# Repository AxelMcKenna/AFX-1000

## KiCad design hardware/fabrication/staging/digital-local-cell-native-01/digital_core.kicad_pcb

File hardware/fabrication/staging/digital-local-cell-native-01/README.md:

# DC02 — local power, filter and reference cells

This selected digital development candidate has **427 missing connections**, down
from 466, with zero native DRC geometry, schematic-parity and ERC findings. Every
native category remains enabled. **Not released for fabrication.**

The 138 electrical parts, five mounts, connector positions, notched 114 × 60 mm
outline and 1.6 mm declared thickness are retained. Three MCP23017 expanders and
39 capacitors/resistors have new explicit sites. The previous expander arrangement
between the Seed solder-pin rows left insufficient nearby space for decouplers.
The ten pot-input filter capacitors now have approximately 2.29 mm local traces
to their Seed pins, instead of 9.6–28.4 mm straight-line separations.

Thirty-nine local connections use 59 new segments and eight 0.60/0.30 mm through
vias. Signal copper remains on the outer faces; both inner layers remain available
for the unfinished power/return design. All eight drilled holes are independently
screened outside front/back SMD copper with at least 0.15 mm hole-edge separation.
This is a geometry screen, not mask-web, plating, registration or stencil approval.

Some local parts use the opposite board face. Their actual routes include the
necessary conventional dogbone vias. The longest current-reference route is
R3002 at 8.864 mm; its placement distance alone must not be used as the routed
length. Its return path and noise sensitivity still require review. The new
connections do not complete ground returns, bulk distribution, exposed-pad
thermal paths, LED current returns or the remaining control/audio/SD signals.

Native source-bound evidence includes [review.json](review.json),
[local-connectivity-review.json](local-connectivity-review.json), the
[additive geometry audit](independent-geometry-audit.json), and
[handoff.json](handoff.json). An independent inverse-transform audit restores all
electrical/mechanical geometry after undoing the 42 declared component changes;
only annotation half-turns are normalized. The full four-sheet schematic is
captured and hashed. The earlier placed-only file lacked persistent pad UUIDs;
the new native checkpoint supplies stable IDs for routing/connectivity evidence.

Both views were inspected at 300 dpi. Thirteen focused integration/audit tests
pass. The [AP02 arrangement](../assembly-layout-02/README.md) rechecks the actual
new poses under the existing conditional receiving limits. Complete installed
fit, actual parts/process acceptance, supply/return and thermal performance,
dynamic fault behavior and final manufacturing/assembly drawings remain open.

The earlier signal-router trial is retained as unselected evidence. Trial 02
incorrectly used reserved inner layers and was rejected. Trial 03 correctly
restricts signal tracks to the outer layers, but uses the superseded remote-cap
placement; its copper is not adopted into DC02.

Revalidate the selected candidate with `python -m hardware.fabrication.audit_scope`.
The next routing capture is `../digital-local-cell-inputs-427/capture.json`.

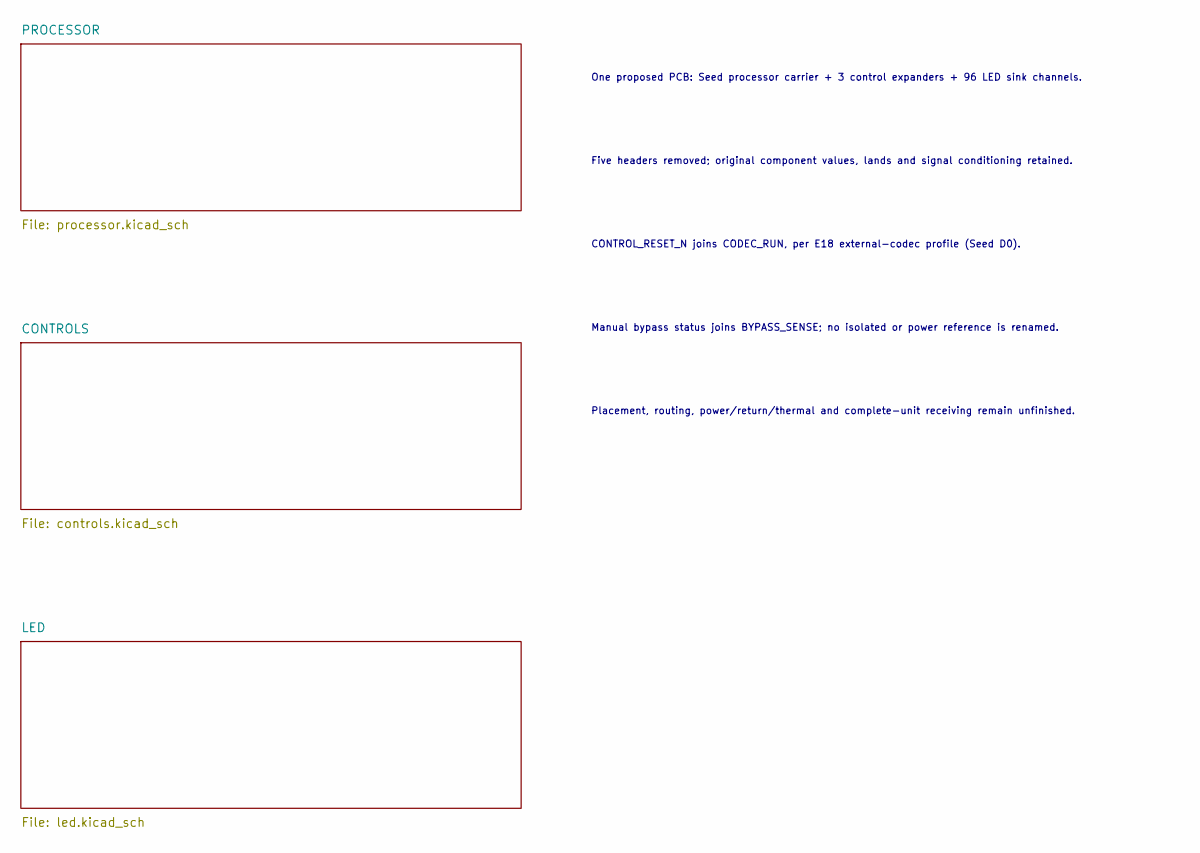
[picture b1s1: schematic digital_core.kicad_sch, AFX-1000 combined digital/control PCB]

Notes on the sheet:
One proposed PCB: Seed processor carrier + 3 control expanders + 96 LED sink channels.
Five headers removed; original component values, lands and signal conditioning retained.
CONTROL_RESET_N joins CODEC_RUN, per E18 external-codec profile (Seed D0).
Manual bypass status joins BYPASS_SENSE; no isolated or power reference is renamed.
Placement, routing, power/return/thermal and complete-unit receiving remain unfinished.

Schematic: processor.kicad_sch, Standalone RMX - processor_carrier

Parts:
C1001: 22uF 25V X7R; C_1210_3225Metric
C1002, C1004, C1006, C1011, C1012, C1013, C1014, C1015, C1016, C1017, C1018, C1019, C1020: 100nF 16V X7R; C_0805_2012Metric
C1003: 1uF 16V X7R; C_0805_2012Metric
C1005: 4.7uF 16V X7R; C_0805_2012Metric
J1001, J1013, J1014, J1015: Alpha6715_AWG18_DIRECT_SOLDER_PROPOSAL; AWG18_Solder_2x1_P4mm_D2p2
J1003, J1006: Header6; PinHeader_1x06_P2.54mm_Vertical
J1004, J1005: Header5; PinHeader_1x05_P2.54mm_Vertical
J1007, J1008: Header2; PinHeader_1x02_P2.54mm_Vertical
J1009, J1010: Header4; PinHeader_1x04_P2.54mm_Vertical
J1012: Header8; PinHeader_1x08_P2.54mm_Vertical
J1020, J1021, J1022, J1023, J1024, J1025, J1026, J1027, J1028, J1029: Header3; PinHeader_1x03_P2.54mm_Vertical
R1001: 0.47R 1% WSLT2512R4700FEA P70=0.815W; WSLT2512_R_2512_Manufacturer
R1002: 10k 1%; R_0805_2012Metric
R1003, R1004, R1005, R1006: 100k 1%; R_0805_2012Metric
R1010, R1011, R1012, R1013, R1014, R1015, R1016, R1017, R1018, R1019, R1020: 33R 1%; R_0805_2012Metric
R1031, R1032, R1033, R1034, R1035, R1036, R1037, R1038, R1039, R1040: 1k 1%; R_0805_2012Metric
R1041, R1042, R1043, R1044, R1045, R1046, R1047, R1048, R1049, R1050: 1M 1%; R_0805_2012Metric
U1001: DaisySeed3; Seed3_Socket40

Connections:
5V_DIG: J1001.1, J1013.1, J1014.1, J1015.1, R1001.1; also elsewhere on the board
/PROCESSOR/ADC_DATA: J1005.4, U1001.32 (D25_ADC_DATA)
/PROCESSOR/ARMED: J1003.5, R1005.1, U1001.37 (D30_ARMED)
/PROCESSOR/BCLK: J1005.2, U1001.35 (D28_BCLK)
/PROCESSOR/DAC_DATA: J1005.5, R1014.2
/PROCESSOR/DAC_DATA_SRC: R1014.1, U1001.33 (D26_DAC_DATA)
/PROCESSOR/GAIN_REQ: J1003.4, R1004.1, U1001.10 (D9)
/PROCESSOR/HEARTBEAT: J1003.2, U1001.14 (D13)
/PROCESSOR/LED_BLANK_SRC: R1013.1, U1001.15 (D14)
/PROCESSOR/LED_MOSI_SRC: R1012.1, U1001.11 (D10)
/PROCESSOR/LED_SCK_SRC: R1011.1, U1001.9 (D8)
/PROCESSOR/LED_XLAT_SRC: R1010.1, U1001.8 (D7)
/PROCESSOR/MCU_PERMIT: J1003.3, R1003.1, U1001.36 (D29_PERMIT)
/PROCESSOR/POT_ADC_00: C1011.1, R1031.2, R1041.1, U1001.22 (D15)
/PROCESSOR/POT_ADC_01: C1012.1, R1032.2, R1042.1, U1001.23 (D16)
/PROCESSOR/POT_ADC_02: C1013.1, R1033.2, R1043.1, U1001.24 (D17)
/PROCESSOR/POT_ADC_03: C1014.1, R1034.2, R1044.1, U1001.25 (D18)
/PROCESSOR/POT_ADC_04: C1015.1, R1035.2, R1045.1, U1001.26 (D19)
/PROCESSOR/POT_ADC_05: C1016.1, R1036.2, R1046.1, U1001.27 (D20)
/PROCESSOR/POT_ADC_06: C1017.1, R1037.2, R1047.1, U1001.28 (D21)
/PROCESSOR/POT_ADC_07: C1018.1, R1038.2, R1048.1, U1001.29 (D22)
/PROCESSOR/POT_ADC_08: C1019.1, R1039.2, R1049.1, U1001.30 (D23)
/PROCESSOR/POT_ADC_09: C1020.1, R1040.2, R1050.1, U1001.31 (D24)
/PROCESSOR/POT_RAW_00: J1020.2, R1031.1
/PROCESSOR/POT_RAW_01: J1021.2, R1032.1
/PROCESSOR/POT_RAW_02: J1022.2, R1033.1
/PROCESSOR/POT_RAW_03: J1023.2, R1034.1
/PROCESSOR/POT_RAW_04: J1024.2, R1035.1
/PROCESSOR/POT_RAW_05: J1025.2, R1036.1
/PROCESSOR/POT_RAW_06: J1026.2, R1037.1
/PROCESSOR/POT_RAW_07: J1027.2, R1038.1
/PROCESSOR/POT_RAW_08: J1028.2, R1039.1
/PROCESSOR/POT_RAW_09: J1029.2, R1040.1
/PROCESSOR/SDMMC_CLK: J1012.8, R1020.2
/PROCESSOR/SDMMC_CLK_SRC: R1020.1, U1001.7 (D6)
/PROCESSOR/SDMMC_CMD: J1012.7, R1019.2
/PROCESSOR/SDMMC_CMD_SRC: R1019.1, U1001.6 (D5)
/PROCESSOR/SDMMC_D0: J1012.3, R1015.2
/PROCESSOR/SDMMC_D0_SRC: R1015.1, U1001.5 (D4)
/PROCESSOR/SDMMC_D1: J1012.4, R1016.2
/PROCESSOR/SDMMC_D1_SRC: R1016.1, U1001.4 (D3)
/PROCESSOR/SDMMC_D2: J1012.5, R1017.2
/PROCESSOR/SDMMC_D2_SRC: R1017.1, U1001.3 (D2)
/PROCESSOR/SDMMC_D3: J1012.6, R1018.2
/PROCESSOR/SDMMC_D3_SRC: R1018.1, U1001.2 (D1)
/PROCESSOR/SEED_VIN: C1001.1, C1002.1, R1001.2, U1001.39 (VIN)
/PROCESSOR/V3V3_ANALOG: C1003.1, C1004.1, J1020.3, J1021.3, J1022.3, J1023.3, J1024.3, J1025.3, J1026.3, J1027.3, J1028.3, J1029.3, U1001.21 (3V3_ANALOG)
/PROCESSOR/WS: J1005.3, U1001.34 (D27_WS)
AGND: C1001.2, C1002.2, C1003.2, C1004.2, C1005.2, C1006.2, C1011.2, C1012.2, C1013.2, C1014.2, C1015.2, C1016.2, C1017.2, C1018.2, C1019.2, C1020.2, J1001.2, J1003.1, J1004.1, J1005.1, J1006.1, J1007.1, J1008.1, J1009.1, J1010.1, J1012.1, J1013.2, J1014.2, J1015.2, J1020.1, J1021.1, J1022.1, J1023.1, J1024.1, J1025.1, J1026.1, J1027.1, J1028.1, J1029.1, R1003.2, R1004.2, R1005.2, R1006.2, R1041.2, R1042.2, R1043.2, R1044.2, R1045.2, R1046.2, R1047.2, R1048.2, R1049.2, R1050.2, U1001.20 (AGND), U1001.40 (DGND); also elsewhere on the board
ANALOG_OK: J1004.4, J1006.6; also elsewhere on the board
BYPASS_SENSE: J1003.6, J1004.3; also elsewhere on the board
CODEC_RUN: J1006.5, R1006.1, U1001.1 (D0); also elsewhere on the board
INPUT_READY: J1004.5, J1007.2; also elsewhere on the board
LED_BLANK: R1002.1, R1013.2; also elsewhere on the board
LED_MOSI: R1012.2; also elsewhere on the board
LED_SCK: R1011.2; also elsewhere on the board
LED_XLAT: R1010.2; also elsewhere on the board
MODE_SEND_RETURN: J1004.2, J1008.2; also elsewhere on the board
SCL: J1006.3, J1009.3, J1010.3, U1001.12 (D11); also elsewhere on the board
SDA: J1006.4, J1009.4, J1010.4, U1001.13 (D12); also elsewhere on the board
V3V3_IO: C1005.1, C1006.1, J1006.2, J1009.2, J1010.2, J1012.2, R1002.2, U1001.38 (3V3_DIGITAL); also elsewhere on the board

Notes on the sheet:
E19 - external-profile Seed3 processor carrier.40 module pins,10 analog pots,control-hub/codec/relay/LED/sensor/SD interfaces.
3.3V outputs are separate: analog pin21 excites pots; digital pin38 powers shared logic. AGND and DGND join on carrier.
Routed150x65mm carrier: front-slot Seed and2mm E18 daughterboard shift implemented in PCB/A05 CAD; physical assembly unverified.
No whole-bus/3.3V load, USB partial-power/backfeed, ADC acquisition/accuracy, SDMMC SI or physical fit approval. No fabrication release.

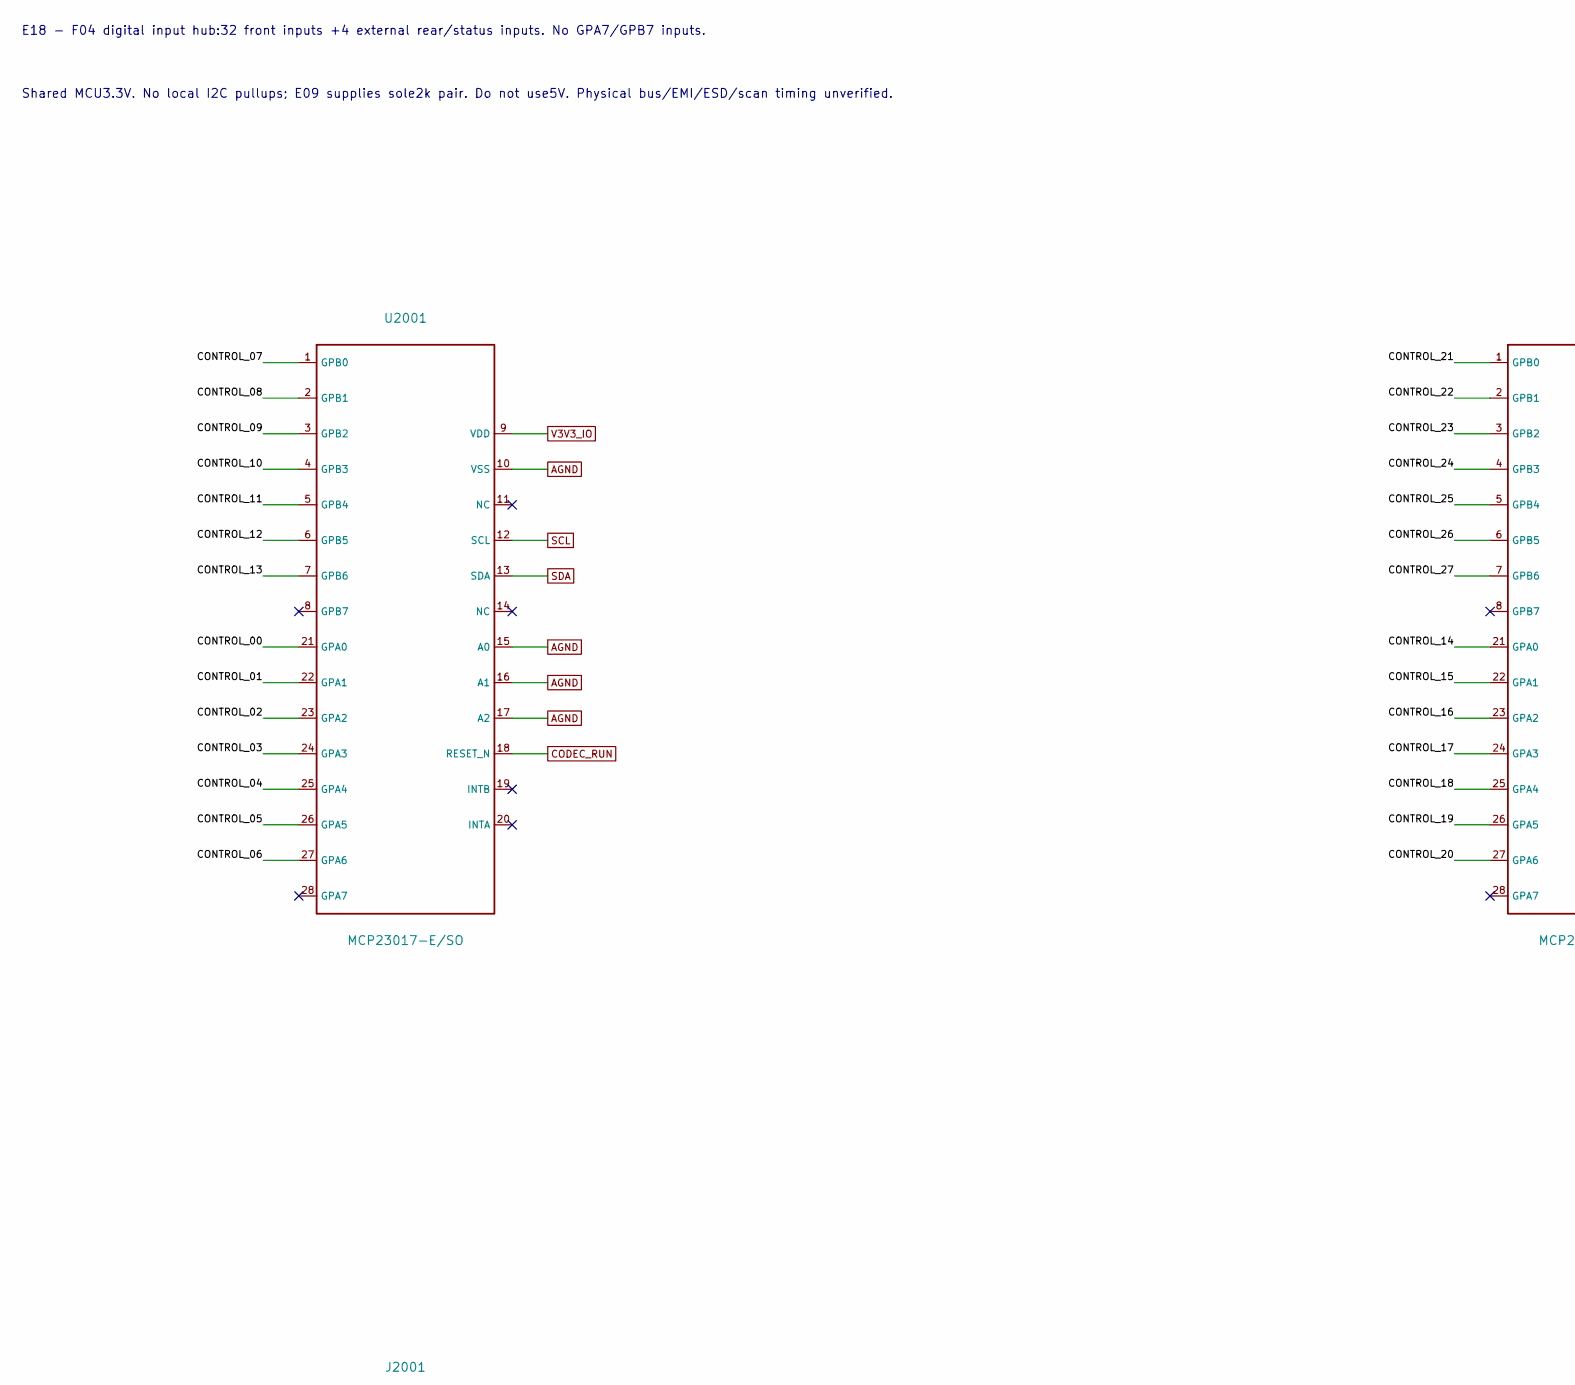
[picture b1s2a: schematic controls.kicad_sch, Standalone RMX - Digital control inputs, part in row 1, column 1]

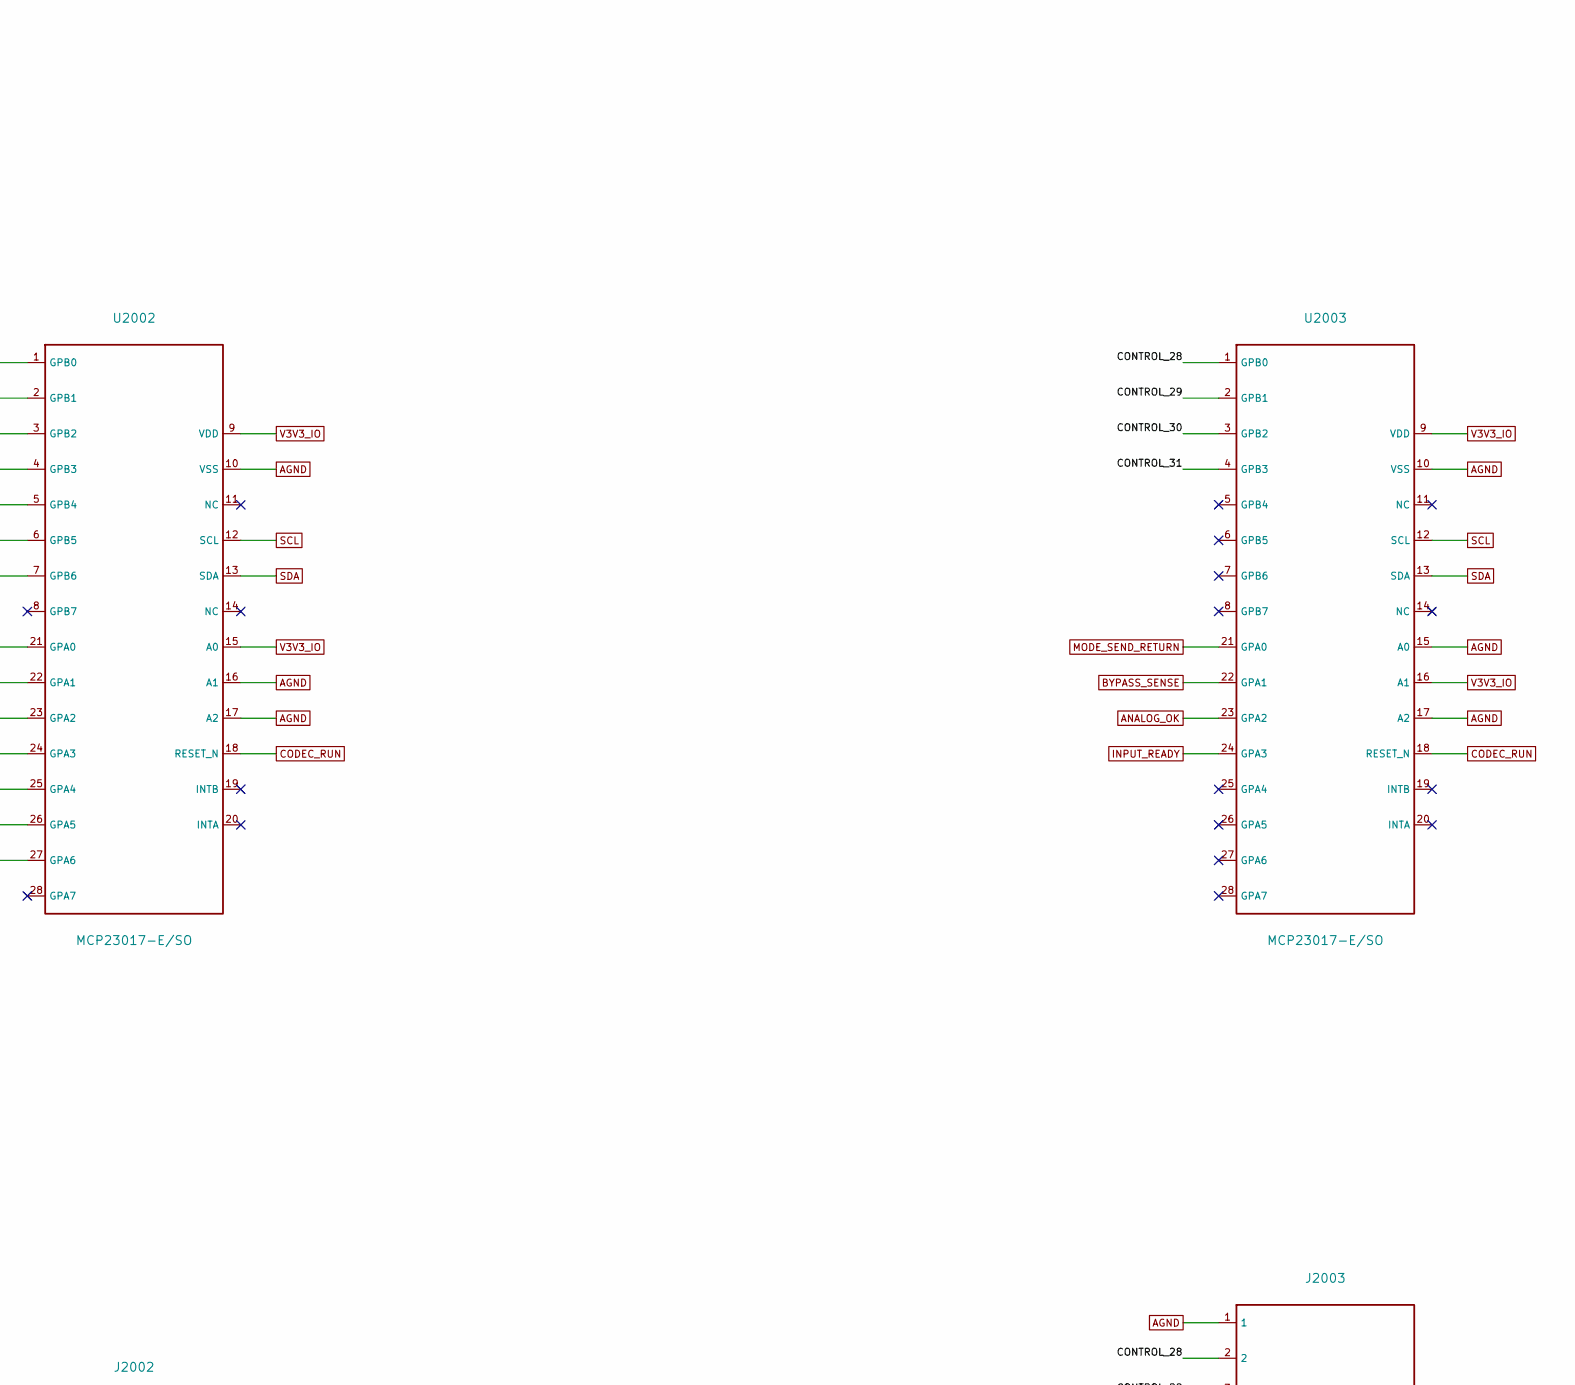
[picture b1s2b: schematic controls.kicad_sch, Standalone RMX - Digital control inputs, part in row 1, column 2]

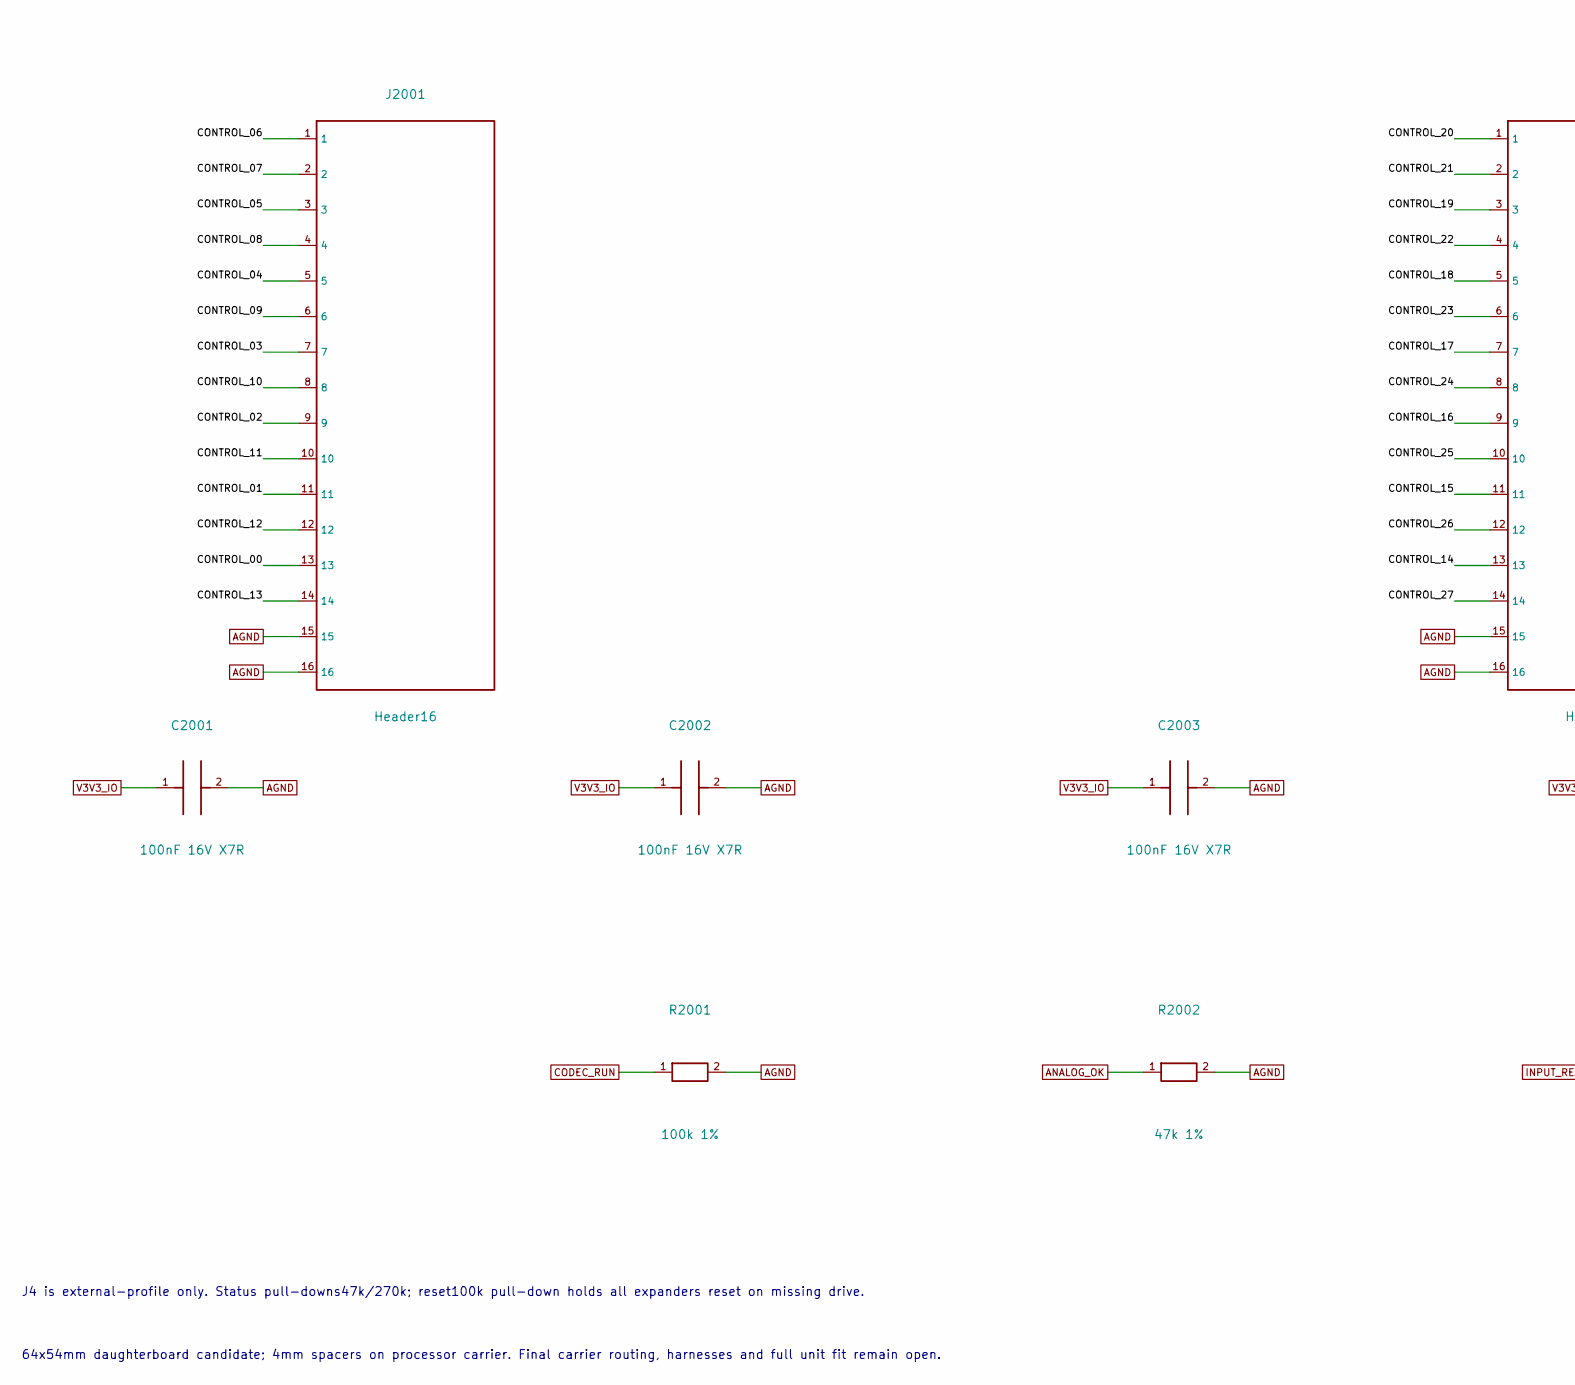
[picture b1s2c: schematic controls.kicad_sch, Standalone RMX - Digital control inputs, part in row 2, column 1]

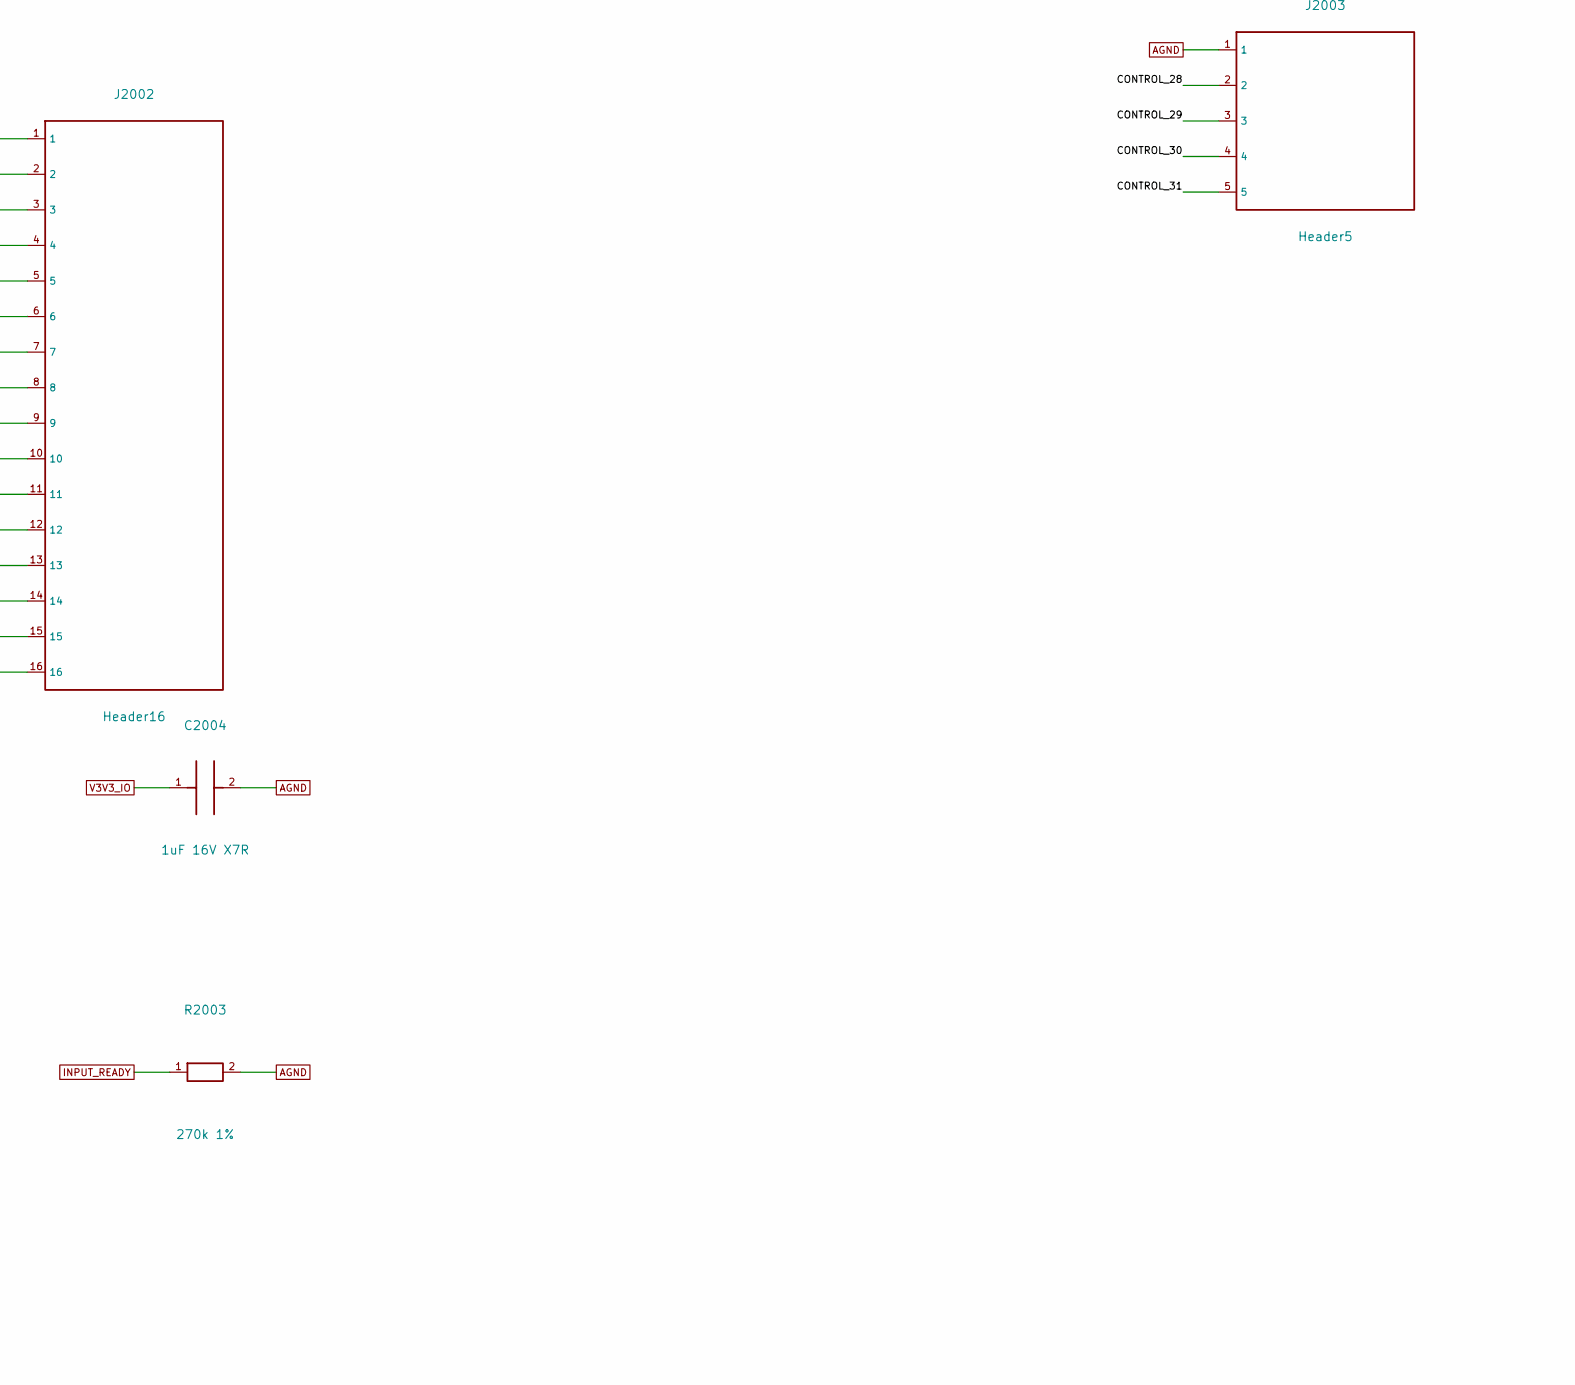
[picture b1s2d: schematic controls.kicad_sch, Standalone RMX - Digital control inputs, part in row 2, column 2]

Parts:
C2001, C2002, C2003: 100nF 16V X7R; C_0805_2012Metric
C2004: 1uF 16V X7R; C_0805_2012Metric
J2001, J2002: Header16; PinHeader_2x08_P2.54mm_Vertical
J2003: Header5; PinHeader_1x05_P2.54mm_Vertical
R2001: 100k 1%; R_0805_2012Metric
R2002: 47k 1%; R_0805_2012Metric
R2003: 270k 1%; R_0805_2012Metric
U2001, U2002, U2003: MCP23017-E/SO; SOIC-28W_7.5x17.9mm_P1.27mm

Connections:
/CONTROLS/CONTROL_00: J2001.13, U2001.21 (GPA0)
/CONTROLS/CONTROL_01: J2001.11, U2001.22 (GPA1)
/CONTROLS/CONTROL_02: J2001.9, U2001.23 (GPA2)
/CONTROLS/CONTROL_03: J2001.7, U2001.24 (GPA3)
/CONTROLS/CONTROL_04: J2001.5, U2001.25 (GPA4)
/CONTROLS/CONTROL_05: J2001.3, U2001.26 (GPA5)
/CONTROLS/CONTROL_06: J2001.1, U2001.27 (GPA6)
/CONTROLS/CONTROL_07: J2001.2, U2001.1 (GPB0)
/CONTROLS/CONTROL_08: J2001.4, U2001.2 (GPB1)
/CONTROLS/CONTROL_09: J2001.6, U2001.3 (GPB2)
/CONTROLS/CONTROL_10: J2001.8, U2001.4 (GPB3)
/CONTROLS/CONTROL_11: J2001.10, U2001.5 (GPB4)
/CONTROLS/CONTROL_12: J2001.12, U2001.6 (GPB5)
/CONTROLS/CONTROL_13: J2001.14, U2001.7 (GPB6)
/CONTROLS/CONTROL_14: J2002.13, U2002.21 (GPA0)
/CONTROLS/CONTROL_15: J2002.11, U2002.22 (GPA1)
/CONTROLS/CONTROL_16: J2002.9, U2002.23 (GPA2)
/CONTROLS/CONTROL_17: J2002.7, U2002.24 (GPA3)
/CONTROLS/CONTROL_18: J2002.5, U2002.25 (GPA4)
/CONTROLS/CONTROL_19: J2002.3, U2002.26 (GPA5)
/CONTROLS/CONTROL_20: J2002.1, U2002.27 (GPA6)
/CONTROLS/CONTROL_21: J2002.2, U2002.1 (GPB0)
/CONTROLS/CONTROL_22: J2002.4, U2002.2 (GPB1)
/CONTROLS/CONTROL_23: J2002.6, U2002.3 (GPB2)
/CONTROLS/CONTROL_24: J2002.8, U2002.4 (GPB3)
/CONTROLS/CONTROL_25: J2002.10, U2002.5 (GPB4)
/CONTROLS/CONTROL_26: J2002.12, U2002.6 (GPB5)
/CONTROLS/CONTROL_27: J2002.14, U2002.7 (GPB6)
/CONTROLS/CONTROL_28: J2003.2, U2003.1 (GPB0)
/CONTROLS/CONTROL_29: J2003.3, U2003.2 (GPB1)
/CONTROLS/CONTROL_30: J2003.4, U2003.3 (GPB2)
/CONTROLS/CONTROL_31: J2003.5, U2003.4 (GPB3)
AGND: C2001.2, C2002.2, C2003.2, C2004.2, J2001.15, J2001.16, J2002.15, J2002.16, J2003.1, R2001.2, R2002.2, R2003.2, U2001.10 (VSS), U2001.15 (A0), U2001.16 (A1), U2001.17 (A2), U2002.10 (VSS), U2002.16 (A1), U2002.17 (A2), U2003.10 (VSS), U2003.15 (A0), U2003.17 (A2); also elsewhere on the board
ANALOG_OK: R2002.1, U2003.23 (GPA2); also elsewhere on the board
BYPASS_SENSE: U2003.22 (GPA1); also elsewhere on the board
CODEC_RUN: R2001.1, U2001.18 (RESET_N), U2002.18 (RESET_N), U2003.18 (RESET_N); also elsewhere on the board
INPUT_READY: R2003.1, U2003.24 (GPA3); also elsewhere on the board
MODE_SEND_RETURN: U2003.21 (GPA0); also elsewhere on the board
SCL: U2001.12 (SCL), U2002.12 (SCL), U2003.12 (SCL); also elsewhere on the board
SDA: U2001.13 (SDA), U2002.13 (SDA), U2003.13 (SDA); also elsewhere on the board
V3V3_IO: C2001.1, C2002.1, C2003.1, C2004.1, U2001.9 (VDD), U2002.9 (VDD), U2002.15 (A0), U2003.9 (VDD), U2003.16 (A1); also elsewhere on the board

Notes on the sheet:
E18 - F04 digital input hub:32 front inputs +4 external rear/status inputs. No GPA7/GPB7 inputs.
Shared MCU3.3V. No local I2C pullups; E09 supplies sole2k pair. Do not use5V. Physical bus/EMI/ESD/scan timing unverified.
J4 is external-profile only. Status pull-downs47k/270k; reset100k pull-down holds all expanders reset on missing drive.
64x54mm daughterboard candidate; 4mm spacers on processor carrier. Final carrier routing, harnesses and full unit fit remain open.

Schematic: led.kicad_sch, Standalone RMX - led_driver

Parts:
C3001, C3003, C3005, C3007, C3009, C3010, C3011, C3012: 100nF 16V X7R; C_0603_1608Metric
C3002, C3004, C3006, C3008, C3014: 4.7uF 16V X7R; C_0805_2012Metric
C3013: 22uF 25V X7R; C_1210_3225Metric
J3002, J3003, J3004, J3005: Header26; PinHeader_2x13_P2.54mm_Vertical
Q3001, Q3002: AO3400A; SOT-23
R3001, R3002, R3003, R3004: 16.5k 1%; R_0603_1608Metric
R3005: 47k 1%; R_0603_1608Metric
R3006, R3007, R3010, R3011: 10k 1%; R_0603_1608Metric
R3008, R3009, R3012, R3013, R3014, R3019, R3020, R3021: 100k 1%; R_0603_1608Metric
R3015, R3016, R3017, R3018: 33R 1%; R_0603_1608Metric
U3001, U3002, U3003, U3004: TLC5947DAPR; TLC5947_DAP0032C
U3005: SN74LVC8T245PWR; TSSOP-24_4.4x7.8mm_P0.65mm
U3006: TPS3808G33DBVR; SOT-23-6
U3007: TPS3808G50DBVR; SOT-23-6

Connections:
5V_DIG: C3001.1, C3002.1, C3003.1, C3004.1, C3005.1, C3006.1, C3007.1, C3008.1, C3010.1, C3012.1, C3013.1, C3014.1, J3002.25, J3002.26, J3003.25, J3003.26, J3004.25, J3004.26, J3005.25, J3005.26, R3007.2, R3011.2, U3001.32 (VCC), U3002.32 (VCC), U3003.32 (VCC), U3004.32 (VCC), U3005.23 (VCCB), U3005.24 (VCCB), U3007.3 (MR_N), U3007.5 (SENSE), U3007.6 (VDD); also elsewhere on the board
/LED/BLANK_5V: R3011.1, R3018.2, U3001.2 (BLANK), U3002.2 (BLANK), U3003.2 (BLANK), U3004.2 (BLANK)
/LED/BLANK_5V_SRC: R3018.1, U3005.18 (B4)
/LED/CLOCK_5V: R3013.1, R3016.2, U3001.3 (SCLK), U3002.3 (SCLK), U3003.3 (SCLK), U3004.3 (SCLK)
/LED/CLOCK_5V_SRC: R3016.1, U3005.20 (B2)
/LED/DATA_5V: R3012.1, R3015.2, U3001.4 (SIN)
/LED/DATA_5V_SRC: R3015.1, U3005.21 (B1)
/LED/ENABLE_MID: Q3001.2 (S), Q3002.3 (D)
/LED/IREF_0: R3001.1, U3001.31 (IREF)
/LED/IREF_1: R3002.1, U3002.31 (IREF)
/LED/IREF_2: R3003.1, U3003.31 (IREF)
/LED/IREF_3: R3004.1, U3004.31 (IREF)
/LED/LATCH_5V: R3014.1, R3017.2, U3001.30 (XLAT), U3002.30 (XLAT), U3003.30 (XLAT), U3004.30 (XLAT)
/LED/LATCH_5V_SRC: R3017.1, U3005.19 (B3)
/LED/LED_00: J3003.1, U3001.5 (OUT0)
/LED/LED_01: J3003.2, U3001.6 (OUT1)
/LED/LED_02: J3003.3, U3001.7 (OUT2)
/LED/LED_03: J3003.4, U3001.8 (OUT3)
/LED/LED_04: J3003.5, U3001.9 (OUT4)
/LED/LED_05: J3003.6, U3001.10 (OUT5)
/LED/LED_06: J3003.7, U3001.11 (OUT6)
/LED/LED_07: J3003.8, U3001.12 (OUT7)
/LED/LED_08: J3003.9, U3001.13 (OUT8)
/LED/LED_09: J3003.10, U3001.14 (OUT9)
/LED/LED_10: J3003.11, U3001.15 (OUT10)
/LED/LED_11: J3003.12, U3001.16 (OUT11)
/LED/LED_12: J3002.12, U3001.17 (OUT12)
/LED/LED_13: J3002.11, U3001.18 (OUT13)
/LED/LED_14: J3002.10, U3001.19 (OUT14)
/LED/LED_15: J3002.9, U3001.20 (OUT15)
/LED/LED_16: J3002.8, U3001.21 (OUT16)
/LED/LED_17: J3002.7, U3001.22 (OUT17)
/LED/LED_18: J3002.6, U3001.23 (OUT18)
/LED/LED_19: J3002.5, U3001.24 (OUT19)
/LED/LED_20: J3002.4, U3001.25 (OUT20)
/LED/LED_21: J3002.3, U3001.26 (OUT21)
/LED/LED_22: J3002.2, U3001.27 (OUT22)
/LED/LED_23: J3002.1, U3001.28 (OUT23)
/LED/LED_24: J3003.13, U3002.5 (OUT0)
/LED/LED_25: J3003.14, U3002.6 (OUT1)
/LED/LED_26: J3003.15, U3002.7 (OUT2)
/LED/LED_27: J3003.16, U3002.8 (OUT3)
/LED/LED_28: J3003.17, U3002.9 (OUT4)
/LED/LED_29: J3003.18, U3002.10 (OUT5)
/LED/LED_30: J3003.19, U3002.11 (OUT6)
/LED/LED_31: J3003.20, U3002.12 (OUT7)
/LED/LED_32: J3003.21, U3002.13 (OUT8)
/LED/LED_33: J3003.22, U3002.14 (OUT9)
/LED/LED_34: J3003.23, U3002.15 (OUT10)
/LED/LED_35: J3003.24, U3002.16 (OUT11)
/LED/LED_36: J3002.24, U3002.17 (OUT12)
/LED/LED_37: J3002.23, U3002.18 (OUT13)
/LED/LED_38: J3002.22, U3002.19 (OUT14)
/LED/LED_39: J3002.21, U3002.20 (OUT15)
/LED/LED_40: J3002.20, U3002.21 (OUT16)
/LED/LED_41: J3002.19, U3002.22 (OUT17)
/LED/LED_42: J3002.18, U3002.23 (OUT18)
/LED/LED_43: J3002.17, U3002.24 (OUT19)
/LED/LED_44: J3002.16, U3002.25 (OUT20)
/LED/LED_45: J3002.15, U3002.26 (OUT21)
/LED/LED_46: J3002.14, U3002.27 (OUT22)
/LED/LED_47: J3002.13, U3002.28 (OUT23)
/LED/LED_48: J3005.1, U3003.5 (OUT0)
/LED/LED_49: J3005.2, U3003.6 (OUT1)
/LED/LED_50: J3005.3, U3003.7 (OUT2)
/LED/LED_51: J3005.4, U3003.8 (OUT3)
/LED/LED_52: J3005.5, U3003.9 (OUT4)
/LED/LED_53: J3005.6, U3003.10 (OUT5)
/LED/LED_54: J3005.7, U3003.11 (OUT6)
/LED/LED_55: J3005.8, U3003.12 (OUT7)
/LED/LED_56: J3005.9, U3003.13 (OUT8)
/LED/LED_57: J3005.10, U3003.14 (OUT9)
/LED/LED_58: J3005.11, U3003.15 (OUT10)
/LED/LED_59: J3005.12, U3003.16 (OUT11)
/LED/LED_60: J3004.12, U3003.17 (OUT12)
/LED/LED_61: J3004.11, U3003.18 (OUT13)
/LED/LED_62: J3004.10, U3003.19 (OUT14)
/LED/LED_63: J3004.9, U3003.20 (OUT15)
/LED/LED_64: J3004.8, U3003.21 (OUT16)
/LED/LED_65: J3004.7, U3003.22 (OUT17)
/LED/LED_66: J3004.6, U3003.23 (OUT18)
/LED/LED_67: J3004.5, U3003.24 (OUT19)
/LED/LED_68: J3004.4, U3003.25 (OUT20)
/LED/LED_69: J3004.3, U3003.26 (OUT21)
/LED/LED_70: J3004.2, U3003.27 (OUT22)
/LED/LED_71: J3004.1, U3003.28 (OUT23)
/LED/LED_72: J3005.13, U3004.5 (OUT0)
/LED/LED_73: J3005.14, U3004.6 (OUT1)
/LED/LED_74: J3005.15, U3004.7 (OUT2)
/LED/LED_75: J3005.16, U3004.8 (OUT3)
/LED/LED_76: J3005.17, U3004.9 (OUT4)
/LED/LED_77: J3005.18, U3004.10 (OUT5)
/LED/LED_78: J3005.19, U3004.11 (OUT6)
/LED/LED_79: J3005.20, U3004.12 (OUT7)
/LED/LED_80: J3005.21, U3004.13 (OUT8)
/LED/LED_81: J3005.22, U3004.14 (OUT9)
/LED/LED_82: J3005.23, U3004.15 (OUT10)
/LED/LED_83: J3005.24, U3004.16 (OUT11)
/LED/LED_84: J3004.24, U3004.17 (OUT12)
/LED/LED_85: J3004.23, U3004.18 (OUT13)
/LED/LED_86: J3004.22, U3004.19 (OUT14)
/LED/LED_87: J3004.21, U3004.20 (OUT15)
/LED/LED_88: J3004.20, U3004.21 (OUT16)
/LED/LED_89: J3004.19, U3004.22 (OUT17)
/LED/LED_90: J3004.18, U3004.23 (OUT18)
/LED/LED_91: J3004.17, U3004.24 (OUT19)
/LED/LED_92: J3004.16, U3004.25 (OUT20)
/LED/LED_93: J3004.15, U3004.26 (OUT21)
/LED/LED_94: J3004.14, U3004.27 (OUT22)
/LED/LED_95: J3004.13, U3004.28 (OUT23)
/LED/OE_N: Q3001.3 (D), R3005.1, U3005.22 (OE_N)
/LED/PG_3V3: Q3001.1 (G), R3006.1, R3008.1, U3006.1 (RESET_N)
/LED/PG_5V: Q3002.1 (G), R3007.1, R3009.1, U3007.1 (RESET_N)
/LED/SERIAL_0: U3001.29 (SOUT), U3002.4 (SIN)
/LED/SERIAL_1: U3002.29 (SOUT), U3003.4 (SIN)
/LED/SERIAL_2: U3003.29 (SOUT), U3004.4 (SIN)
AGND: C3001.2, C3002.2, C3003.2, C3004.2, C3005.2, C3006.2, C3007.2, C3008.2, C3009.2, C3010.2, C3011.2, C3012.2, C3013.2, C3014.2, Q3002.2 (S), R3001.2, R3002.2, R3003.2, R3004.2, R3008.2, R3009.2, R3012.2, R3013.2, R3014.2, R3019.2, R3020.2, R3021.2, U3001.1 (GND), U3001.33 (EP), U3002.1 (GND), U3002.33 (EP), U3003.1 (GND), U3003.33 (EP), U3004.1 (GND), U3004.33 (EP), U3005.7 (A5), U3005.8 (A6), U3005.9 (A7), U3005.10 (A8), U3005.11 (GND), U3005.12 (GND), U3005.13 (GND), U3006.2 (GND), U3007.2 (GND); also elsewhere on the board
LED_BLANK: R3010.1, U3005.6 (A4); also elsewhere on the board
LED_MOSI: R3019.1, U3005.3 (A1); also elsewhere on the board
LED_SCK: R3020.1, U3005.4 (A2); also elsewhere on the board
LED_XLAT: R3021.1, U3005.5 (A3); also elsewhere on the board
V3V3_IO: C3009.1, C3011.1, R3005.2, R3006.2, R3010.2, U3005.1 (VCCA), U3005.2 (DIR), U3006.3 (MR_N), U3006.5 (SENSE), U3006.6 (VDD); also elsewhere on the board

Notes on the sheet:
E20 -96-channel constant-current LED/display driver. MCU->U1->U2->U3->U4; global n uses chip n/24 and OUT(n%24).
5V powers driver logic and common anodes; dual-supply translator isolates processor3.3V. Both rails must qualify before outputs enable.
Proposed91x27mm PCB at(197,77), seat6.5mm beneath scene controls; exact footprints/PCB/fit remain to be verified.
3mA is nominal, not a guaranteed low-current bound. E14/E17 digital power budget must include driver ICC. No fabrication or physical validation approval.

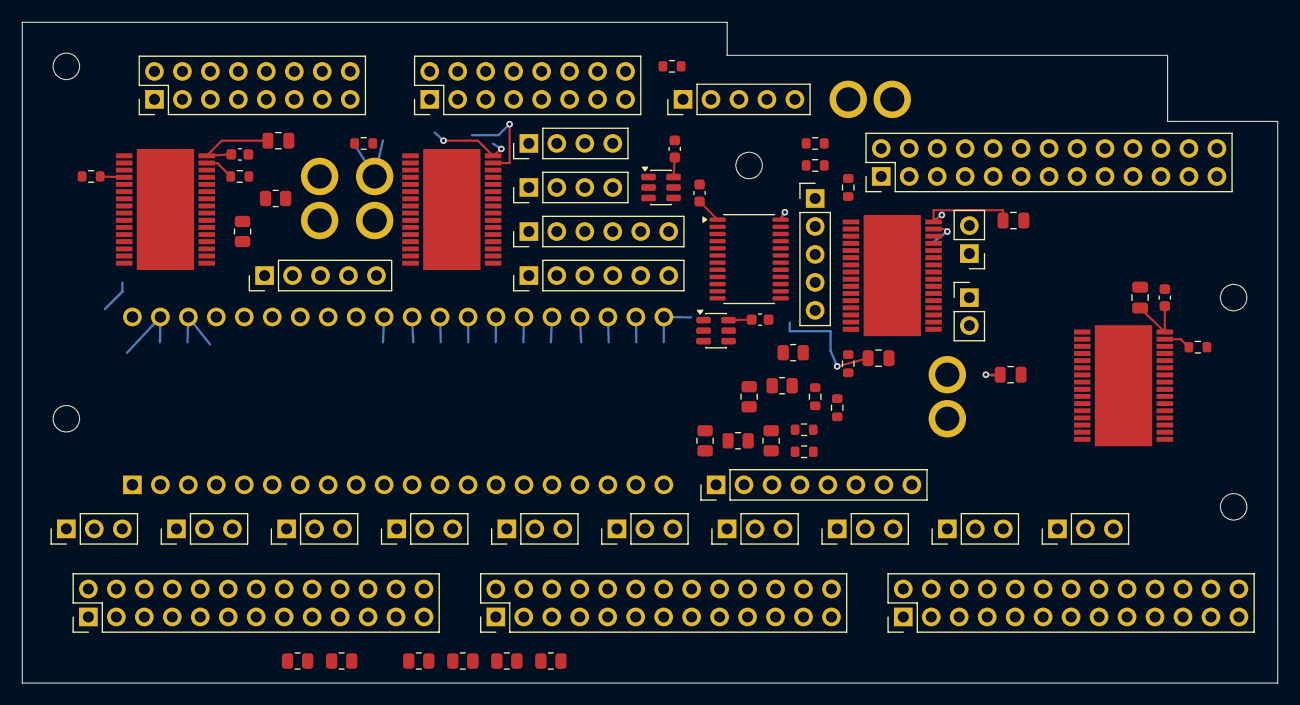
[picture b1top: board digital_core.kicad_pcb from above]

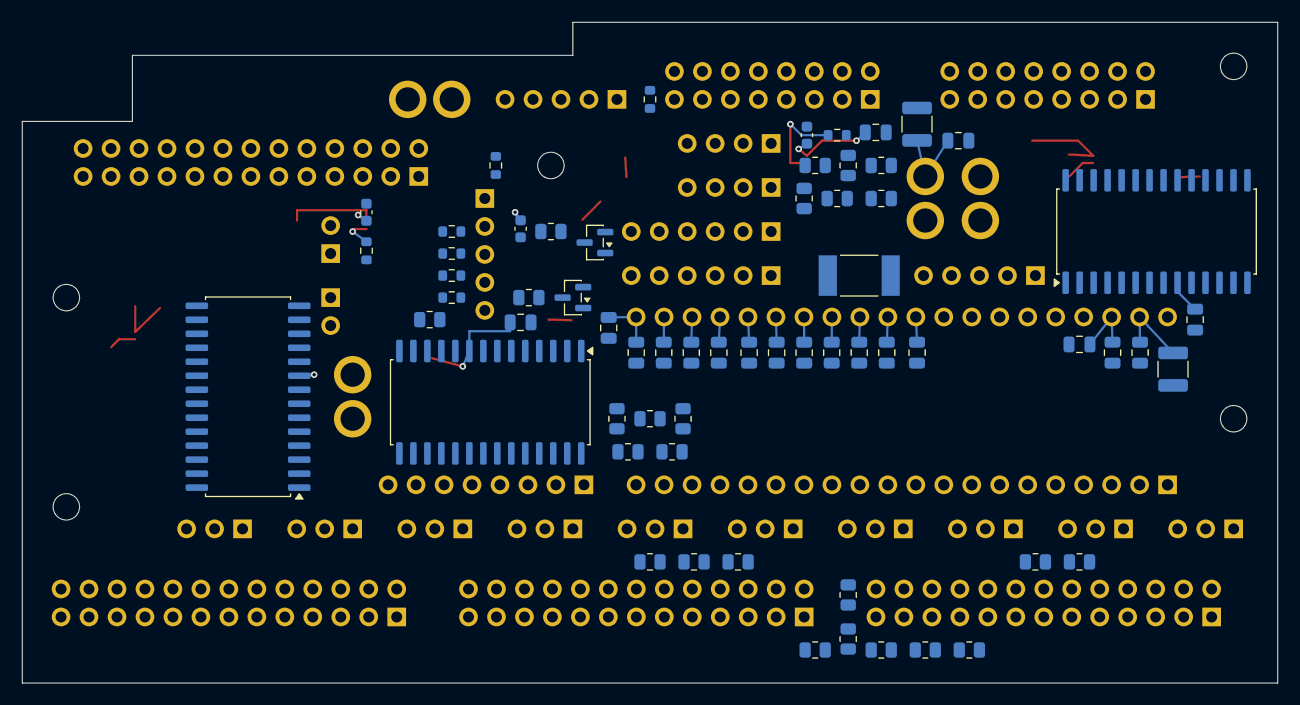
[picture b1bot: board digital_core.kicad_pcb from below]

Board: 4 copper layers, 114.0 x 60.0 mm, 143 parts (63 on the bottom side), 208 nets.

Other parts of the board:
H1, H2, H3, H4, H5: M2_CLEARANCE; M2_Clearance

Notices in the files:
parts and their libraries:
Seed3 + 2xSSW-120-02-G-S: official Daisy pad centers/numbering, 1.04mm socket holes per Samtec ssw-s.pdf. Seed3/USB/stack bounds modeled separately. Electrosmith MIT license in vendor/Electrosmith-LICENSE.txt.
